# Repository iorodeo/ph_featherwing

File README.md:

# IO Rodeo pH Feather Wing

Hardware design for IO Rodeo's pH Feather Wing (in development).

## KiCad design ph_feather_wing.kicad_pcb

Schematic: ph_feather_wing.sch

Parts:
C1: 1uF; C_0603_1608Metric_Pad1.05x0.95mm_HandSolder
C2, C3: 0.1uF; C_0603_1608Metric_Pad1.05x0.95mm_HandSolder
J1: Conn_Coaxial; BNC
J2: Screw_Terminal_01x03; CONNBLOCK3
R1, R2: 10K; R_0603_1608Metric_Pad1.05x0.95mm_HandSolder
R3: 1k; R_0603_1608Metric_Pad1.05x0.95mm_HandSolder
R4: 4.7k; R_0603_1608Metric_Pad1.05x0.95mm_HandSolder
SW1, SW2: SW_Push; KMR7_SWITCH
U1, U2: LMP7721; SOIC-8_3.9x4.9mm_P1.27mm_HandSolder
W1: feather_wing

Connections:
/3V3: C2.1, C3.1, J2.2, R1.1, R4.1, U1.6, U2.6, W1.14 (3V)
/BUTTON_1: SW1.1, W1.8 (D12)
/BUTTON_2: SW2.1, W1.9 (D13)
/PH_VOUT: C1.2, R3.2, W1.19 (A2)
/PROBE_OUT: J1.1 (In), U2.1
/PROBE_VGND: J1.2 (Ext), U1.4, U1.8
/TEMP_DATA: J2.1, R4.2, W1.7 (D11)
GND: C1.1, C2.2, C3.2, J2.3, R2.2, SW1.2, SW2.2, U1.3, U2.3, W1.16 (GND)
unnamed: R1.2, R2.1, U1.1
unnamed: R3.1, U2.2, U2.4, U2.7, U2.8

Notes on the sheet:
Design based on "AN-1852 Designing With pH Electrodes" http://www.ti.com/lit/an/snoa529a/snoa529a.pdf
PH PROBE CONNECTOR
OPTIONAL DS18B20 TEMPERATURE SENSOR
CALIBRATION PUSHBUTTONS
C&K PN KMR742NG LFS Digikey CKN10689CT-ND

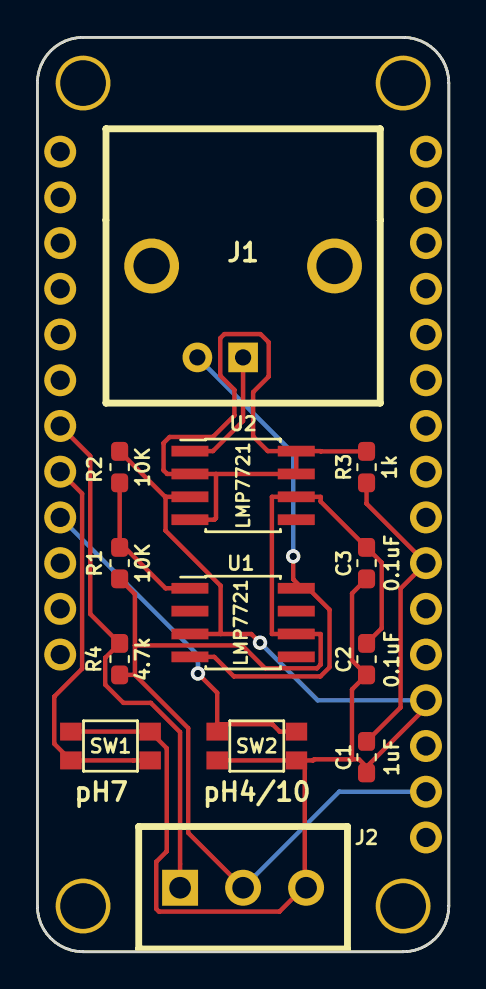
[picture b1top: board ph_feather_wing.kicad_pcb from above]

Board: 2 copper layers, 22.9 x 50.8 mm, 14 parts (0 on the bottom side), 10 nets.

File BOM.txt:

Part        Description                 Package     Vendor    Part Number             Qty
----        -----------------------     -------     ------    -----------             ---
C1          1uF ceramic capacitor       0603        Digikey   1276-1036-1-ND           1 
C2,C3       0.1uF ceramic capacitor     0603        Digikey   399-1096-1-ND            2 
J1          BNC connector               NA          Digikey   A97555-ND                1 
J2          3-pos screw terminal        NA          Digikey   ED2636-ND                1 
R1,R2       10k resistor, 0.1%          0603        Digikey   P10KDBCT-ND              2 
R3          1k resistor, 1%             0603        Digikey   MCT0603-1.00K-CFCT-ND    1 
R4          4.7k resistor, 5%           0603        Digikey   311-4.7KGRCT-ND          1 
SW1,SW2     switch tactile SPST-NO      NA          Digikey   CKN10689CT-ND            2 
U1,U2       LMP7721 op amp              8-SOIC      Digikey   CKN10689CT-ND            2

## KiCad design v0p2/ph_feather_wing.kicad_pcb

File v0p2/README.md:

# IO Rodeo pH Feather Wing

Hardware design for IO Rodeo's pH Feather Wing (in development).

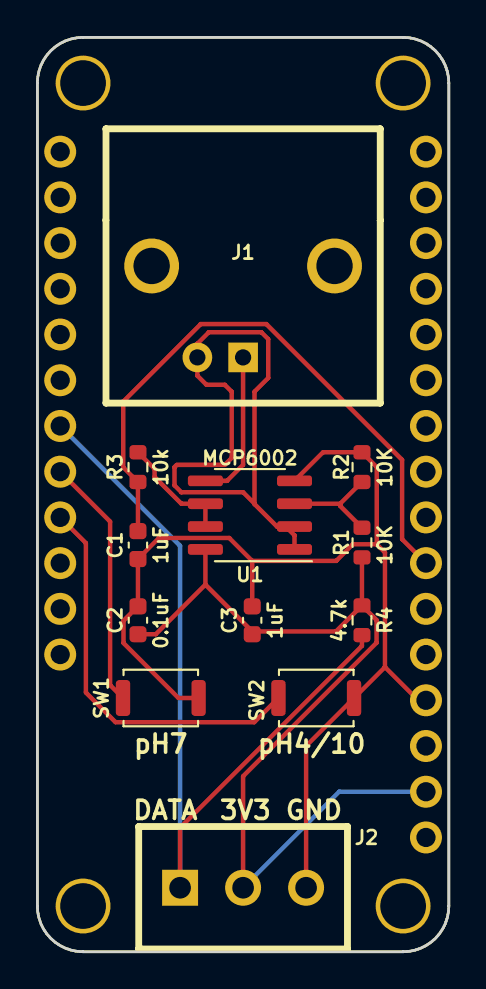
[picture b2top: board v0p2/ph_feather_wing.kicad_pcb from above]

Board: 2 copper layers, 22.9 x 50.8 mm, 13 parts (0 on the bottom side), 10 nets.

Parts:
C1, C3: 1uF; C_0603_1608Metric
C2: 0.1uF; C_0603_1608Metric
J1: Conn_Coaxial; BNC
J2: Screw_Terminal_01x03; CONNBLOCK3
R1, R2: 10K; R_0603_1608Metric
R3: 10k; R_0603_1608Metric
R4: 4.7k; R_0603_1608Metric
SW1, SW2: SW_Push; SW_Push_SPST_NO_Alps_SKRK
U1: MCP6002; SOIC-8_3.9x4.9mm_P1.27mm
W1: feather_wing

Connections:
/3V3: C2.1, C3.1, J2.2, R1.1, R4.1, U1.8, W1.14
/BUTTON_1: SW1.1, W1.8
/BUTTON_2: SW2.1, W1.9
/PH_VOUT: C1.2, R3.1, W1.19
/PROBE_OUT: J1.1, U1.5
/PROBE_VGND: J1.2, U1.1, U1.2
/TEMP_DATA: J2.1, R4.2, W1.7
GND: C1.1, C2.2, C3.2, J2.3, R2.2, SW1.2, SW2.2, U1.4, W1.16
unnamed: R1.2, R2.1, U1.3
unnamed: R3.2, U1.6, U1.7

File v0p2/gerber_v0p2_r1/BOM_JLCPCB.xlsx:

Comment | Designator | Footprint | LCSC Part #（optional） | Qty
1uF ceramic capacitor | C1, C3 | 603 | C15849 | 2
0.1uF ceramic capacitor | C2 | 603 | C14663 | 1
10k resistor 0.1% | R1, R2, R3 | 603 | C190321 | 3
4.7k resistor 1% | R4 | 603 | C23162 | 1
switch SPST-NO | SW1, SW2 | SW-SMD-2_2.9x3.9x1.7 | C115357 | 2
MCP6002T-I/SN opamp | U1 | SOIC-8_3.9x4.9x1.27P | C7377 | 1

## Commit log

2019-02-22 Project creation.
2019-02-28 Added BOM.
2019-03-17 Fixed part number issue in BOM.
2019-04-01 Add pdf of schematic.
2020-07-28 Fixed issue with readme caused by move to github. Added .gitignore file.
2021-01-17 Made back sild visible again.
2021-01-17 Rearranged project and began working on v0.2 of the design.
2021-01-18 Finished preliminary draft of version 0.2 R1.
2021-01-18 Added guard ring, re-routed, made r1 gerbers, added files for assembly.
2021-01-18 Added .zip of gerbers. Fixed minor issues with assembly files.
2021-01-18 Fixed component orientation in CPL file.
2021-02-23 Added pdf of schematic for new version of the PCB.
2021-02-23 Added image of V0.2 design.
